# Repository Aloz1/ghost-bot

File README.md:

# Ghost-Bot
A simple line following robot that can be hacked together easily and raced for the ultimate nerd (that's a term of endearment around here) street cred. 

https://github.com/ChrisAlphabet/ghost-bot/assets/16814545/d810597f-699b-4427-b444-a860e60cc908

## Motivation
I like building things and I like hanging out with the Ghost Bat crew. Adam has done an excellent job of organising DCS Friday's (regardless of my lack of attendance) and has inspired me to try and do a similar thing with some hands on robotics/electronics/software workshops.

## Requirements
* Beginner friendly
    * Arduino based
    * Through hole components
    * No specialized equipment
* Low cost
    * "The best part is no part"
    * Build it, break it, repair it, build another one
* Able to be completed in a weekend
    * No Gantt chart required
    * Easier to herd the cats 

## Assembly
* Don't touch the hot end of the soldering iron

## We need you!
We need volunteers to perform V&V and see if we:
* Built the thing right
* Built the right thing

## How to order parts on Element 14
TODO add an instruction on how to use the BOM upload tool

## Credit
This robot is ~~shamelessly plagarised~~ inspired by a line following robot I built during my first year at uni. If Dr. Robert Ross ever sees this (anything can happen on the internet), thanks! I somehow misplaced the original, so any mistakes are mine and mine alone.

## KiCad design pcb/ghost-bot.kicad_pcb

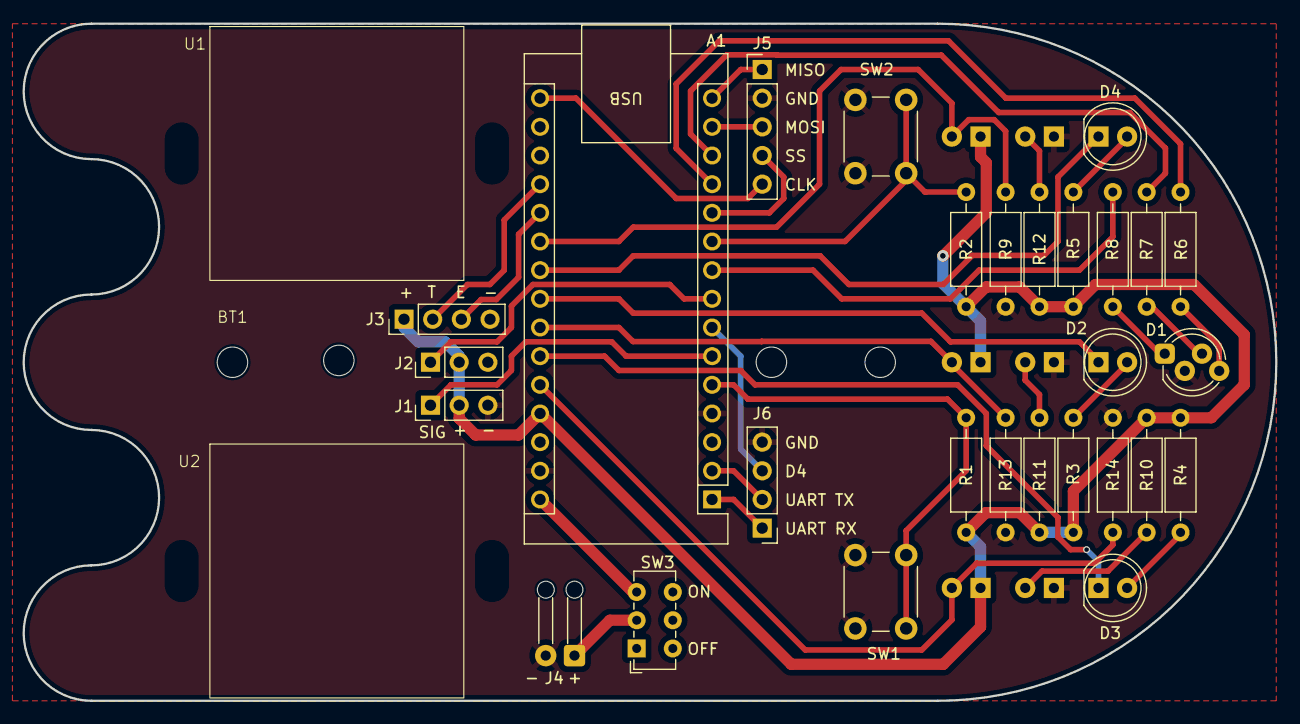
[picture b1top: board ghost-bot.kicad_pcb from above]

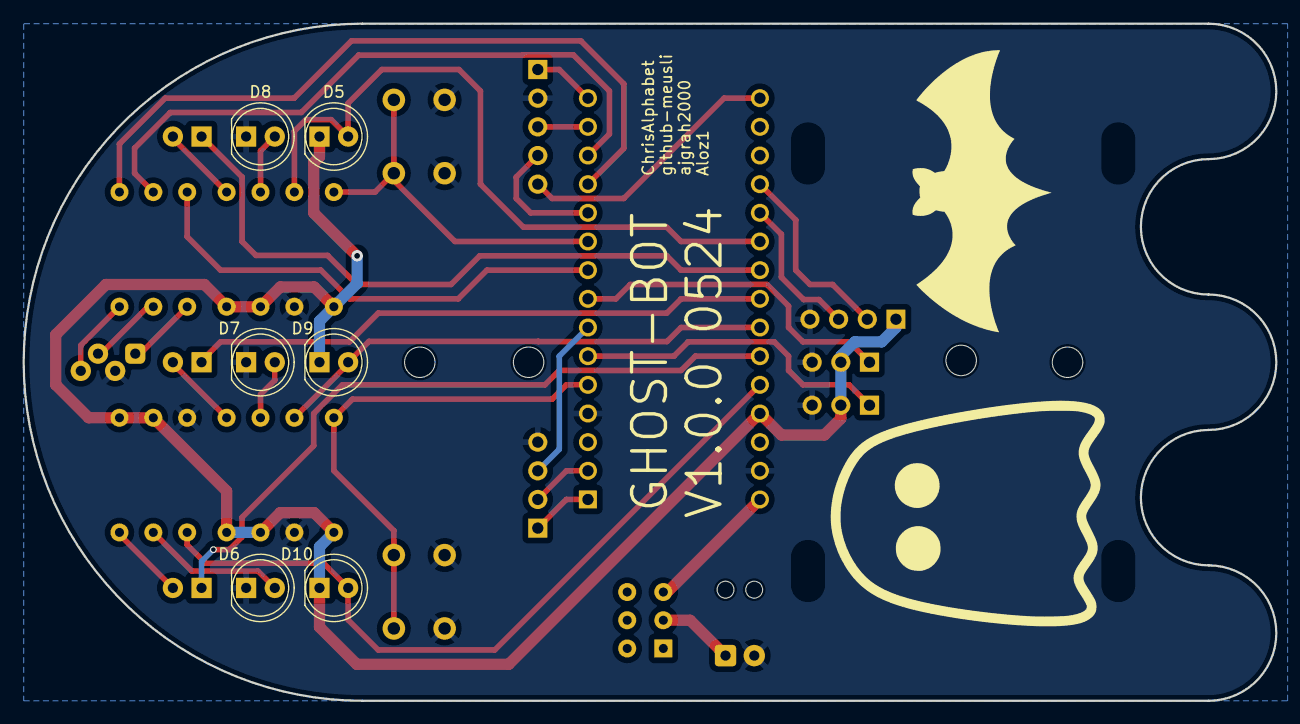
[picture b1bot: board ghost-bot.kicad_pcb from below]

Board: 2 copper layers, 111.0 x 60.0 mm, 37 parts (6 on the bottom side), 35 nets.

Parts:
A1: Arduino_Nano_v3.x; Arduino_Nano
BT1: Battery Holder; Keystone 2478 Battery Holder
D1: LED_BKGR; LED_D5.0mm-4_RGB_Staggered_Pins_fixed-silkscreen
D2, D3, D4: LED; LED_D5.0mm
D5, D9, D10: D_Photo; LED_D5.0mm_Clear
D6, D7, D8: IR LED; LED_D5.0mm_IRBlack
J1, J2: Conn_01x03_Pin; PinHeader_1x03_P2.54mm_Vertical
J3, J6: Conn_01x04_Pin; PinHeader_1x04_P2.54mm_Vertical
J4: Conn_01x02_Pin; SolderWire-0.1sqmm_1x02_P2.54mm_D0.4mm_OD1mm_Relief
J5: Conn_01x05_Pin; PinHeader_1x05_P2.54mm_Vertical
R1, R2: 10k; R_Axial_DIN0207_L6.3mm_D2.5mm_P10.16mm_Horizontal
R3, R4, R5: 330R; R_Axial_DIN0207_L6.3mm_D2.5mm_P10.16mm_Horizontal
R6: 150R; R_Axial_DIN0207_L6.3mm_D2.5mm_P10.16mm_Horizontal
R7, R8, R10, R11, R12: 100R; R_Axial_DIN0207_L6.3mm_D2.5mm_P10.16mm_Horizontal
R9, R13, R14: 100k; R_Axial_DIN0207_L6.3mm_D2.5mm_P10.16mm_Horizontal
SW1, SW2: SW_Push; SW_PUSH_6mm
SW3: Switch; SW_E-Switch_EG1271_SPDT
U1: SG90 Mount Left
U2: SG90 Mount Right

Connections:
+5V: A1.27 (+5V), D5.1 (K), D9.1 (K), D10.1 (K), J1.2, J2.2, J3.1, R1.2, R2.2, R3.1, R4.1, R5.1, R10.1, R11.1, R12.1
+BATT: J4.1, SW3.2 (B)
+BATT_SW: A1.30 (VIN), SW3.3 (A)
/ECHO: A1.20 (A1), J3.3
/GPIO_D4: A1.7 (D4), J6.3
/LED0: A1.23 (A4), D2.1 (K)
/LED1: A1.25 (A6), D3.1 (K)
/LED2: A1.22 (A3), D4.1 (K)
/PD0: A1.21 (A2), D5.2 (A), R9.2
/PD1: A1.24 (A5), D9.2 (A), R13.2
/PD2: A1.26 (A7), D10.2 (A), R14.2
/PUSH_BTN0: A1.5 (D2), R1.1, SW1.2
/PUSH_BTN1: A1.10 (D7), R2.1, SW2.2
/RGB_B: A1.9 (D6), R8.2
/RGB_G: A1.13 (D10), R7.2
/RGB_R: A1.12 (D9), R6.2
/SERVO0: A1.6 (D3), J1.1
/SERVO1: A1.8 (D5), J2.1
/SPI_CLK: A1.16 (D13), J5.5
/SPI_MISO: A1.15 (D12), J5.1
/SPI_MOSI: A1.14 (D11), J5.3
/SPI_SS: A1.11 (D8), J5.4
/TRIG: A1.19 (A0), J3.2
/UART_RX: A1.1 (D1/TX), J6.1
/UART_TX: A1.2 (D0/RX), J6.2
GND: A1.4 (GND), A1.29 (GND), D1.2 (K), D6.1 (K), D7.1 (K), D8.1 (K), J1.3, J2.3, J3.4, J4.2, J5.2, J6.4, R9.1, R13.1, R14.1, SW1.1, SW2.1
unnamed: D1.1 (BA), R8.1
unnamed: D1.3 (GA), R7.1
unnamed: D1.4 (RA), R6.1
unnamed: D2.2 (A), R3.2
unnamed: D3.2 (A), R4.2
unnamed: D4.2 (A), R5.2
unnamed: D6.2 (A), R10.2
unnamed: D7.2 (A), R11.2
unnamed: D8.2 (A), R12.2

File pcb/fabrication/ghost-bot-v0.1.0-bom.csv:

"Reference","Value","Qty","DNP","Supplier Part Number","Manufacturer Part Number","Supplier "
"A1","Arduino_Nano_v3.x","1","","1848691","A000005","Element 14"
"BT1","Battery Holder","1","","1650685","2478","Element 14"
"D1","LED_BKGR","1",""," 2290374"," L-154A4SURKQBDZGW","Element 14"
"D2,D3,D4","LED","3","","1581138"," MCL053GD","Element 14"
"D5,D9,D10","D_Photo","3","","1212743","SFH203-FA","Element 14"
"D6,D7,D8","IR LED","3","","1716710","OFL-5102","Element 14"
"J1,J2","Conn_01x03_Pin","2",""," 1593412","2211S-03G","Element 14"
"J3","Conn_01x04_Pin","1","","1593413","2211S-04G","Element 14"
"J4","Conn_01x02_Pin","1","","NA","NA","NA"
"R1,R2","10k","2","","9339060","MCF 0.25W 10K","Element 14"
"R3,R4,R5","330R","3","","9341730","MF25 330R","Element 14"
"R6","150R","1","","9339175","MCF 0.25W 150R","Element 14"
"R7,R8,R10,R11,R12","100R","5","","9339043","MCF 0.25W 100R","Element 14"
"R9,R13,R14","100k","3","","9341129","MF25 100K","Element 14"
"SW1,SW2","SW_Push","2","","2456210","1825910-6","Element 14"
"SW3","Switch","1","","4050998","EG1271","Element 14"
"U1,U2","~","2","","3359812","MP-708-0002","Element 14"

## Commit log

2024-03-06 Init commit of schematic
2024-03-06 Connect IR LEDs to GND
2024-03-07 Breakout unused pins, add extra power pins
2024-03-07 Init commit of through-hole pcb
2024-03-22 Add ghost outline edgecut, place components
2024-04-01 Random commit before refactoring
2024-04-01 Simplify circuit, add battery holder mounting points
2024-04-01 Add footprints for servos
2024-04-06 Minor placement changes, add strain relief for battery wires
2024-04-06 WIP commit before changing layout
2024-04-07 Add initial routing
2024-04-07 Fix unconnected net
2024-04-07 Change +5V from pour to route
2024-04-07 Update power switch
2024-04-07 Add version number and blank space for name
2024-04-07 Fix servo 3d model, add battery holder 3d model
2024-04-07 Add 3d model to slide switch
2024-04-11 Replace battery connector with footprints that include strain relief, change rgb led footprint
2024-04-11 Add missing save in the schematic (footprint change)
2024-04-12 Create a template wheel with stl ans STEP exports.
2024-04-12 Minor silkscreen changes before generating gerbers/drill
2024-04-12 Add gerber and drill files
2024-04-12 Update rev to 0.1.0, update silkscreen to match and re-gen fab outputs
2024-04-12 Add version number to fab outputs
2024-04-13 Add part numbers to schematic, remove csv from gitignore, generate csv bom
2024-04-16 Remove part to remember, now included in bom
2024-04-16 Update 330 and 100k resistor part numbers for parts that are available now
2024-04-16 Add invoice for e14 parts purchase
2024-04-16 Add Bryan's sweet wheel to the servo 3d model, export as step
2024-04-17 Add pdfs of schematic and pcb, regenerate step
2024-04-17 Fix servo highlighting
2024-04-19 Run a plugin that archives 3d models to a project folder
2024-04-23 Trying a simple github action.
2024-04-23 Fixing path for schematic in kicad cli command.
2024-04-23 Adding token to allow release creation for github action.
2024-04-23 Fixed name
2024-05-05 Update PR branch name to main, add ability to be triggered manually
2024-05-05 Add a simple example to experiment with manual triggers
2024-05-05 Dont run action on push
2024-05-05 Add kicad render action that I saw on hackaday
2024-05-05 Update gh pages url
2024-05-05 Use local ref name to test build
2024-05-05 Address deprecation warnings and rename action
2024-05-05 Update ref to main
2024-05-05 Run action on pull request into main
2024-05-05 Revert version to see if it fixes generation issue
2024-05-05 Add video to README.md
2024-05-05 Add new lines so video renders in README.md
2024-05-08 Issue-6: Move LEDs, breakout unused pins
2024-05-11 Separate UART and SPI connectors, reroute tracks, move buttons
2024-05-18 Add a script that generates gerber drill files
2024-05-18 Add step export to fab outputs
2024-05-18 Resolve gnd thermal relief issues
2024-05-19 Add ability to generate schematic pdf, pcb pdf, bom and drc reports to script
2024-05-19 Add options to shell script
2024-05-19 Rename output script and plumb into existing github action
2024-05-19 Make output script executable by workflow
2024-05-19 Add missing argument to script
2024-05-19 Attempt to workaround release issue
2024-05-19 Zip output before release
2024-05-19 Remove local outputs now that they can be generated using a github action
2024-05-20 Change LED pins (again)
2024-05-21 Add ERC to generated outputs, update readme
2024-05-21 Update silkscreen
2024-05-21 Update PCB title
2024-05-21 Minor adjustment to silkscreen images
2024-05-24 Add manufacturer, supplier and supplier part number to BOM output
2024-05-25 Fix grouping by supplier part number
2024-05-25 Add screws and standoffs to sch to include them in the bom
2024-05-25 Add headers for arduino to plug into so they show up in the bom
2024-05-25 Update battery holder footprint
2024-05-25 Rework traces/placement to work around updated hole positions
2024-10-06 Change battery terminal to 2.54mm pitch. Allows "JST" style connector
